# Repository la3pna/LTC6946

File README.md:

# LTC6946
LTC6946 PLL PCB + control library.

Made for using LTC6946 in the multisynth application with Si5351 as the clock generator (gives sub 1Hz resolution to 6GHz).

Does not seem to be finished, not sure if there is lacking some code? (dec 28, 2018)

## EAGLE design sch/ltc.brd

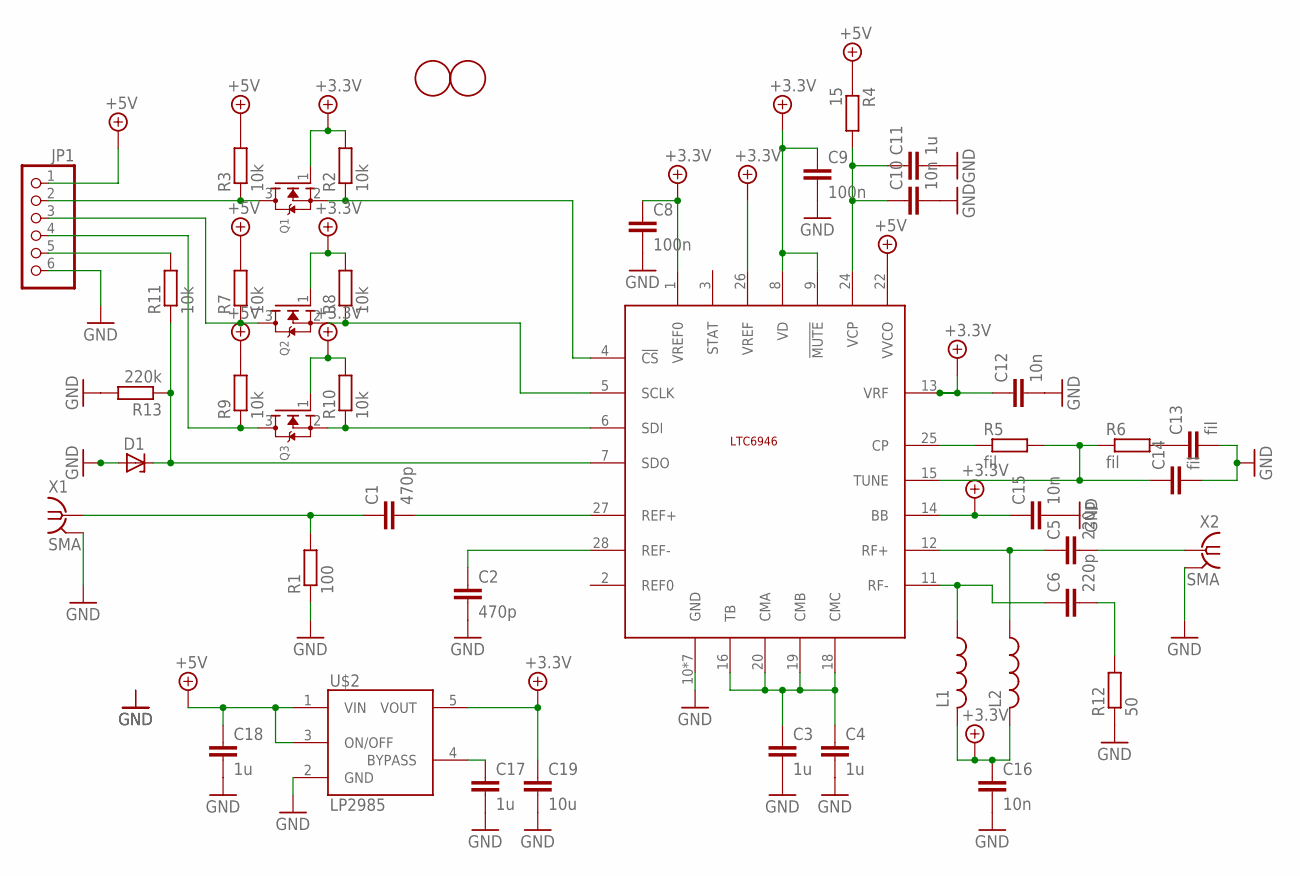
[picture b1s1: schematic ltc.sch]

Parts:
C1, C2: 470p; C0603
C3, C4, C11, C17, C18: 1u; C0603
C5, C6: 220p; C0603
C8, C9: 100n; C0603
C10, C12, C15, C16: 10n; C0603
C13, C14: fil; C0603
C19: 10u; C0603
D1: ZENER-DIODESOT23; SOT23
JP1: PINHD-1X6B; 1X06-BIG
L1, L2: L-USL2825P; L2825P
Q1, Q2, Q3: MOSFET-NREFLOW; SOT23
R1: 100; R0603
R2, R3, R7, R8, R9, R10, R11: 10k; R0603
R4: 15; R0603
R5, R6: fil; R0603
R12: 50; R0603
R13: 220k; R0603
U$1: LTC6946; QFN28-UFD
U$2: LP2985AIM5-3.3; SOT25
U$3, U$4: FIDUCIAL; FIDUCIAL_1MM
X1, X2: SMA; J502-ND-142-0711-821/826

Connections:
+4.1V: C8.1, C9.1, C12.1, C15.1, C16.1, C19.1, L1.2, L2.2, Q1.1 (G), Q2.1 (G), Q3.1 (G), R2.2, R8.2, R10.2, U$1.1 (VREF0), U$1.8 (VD), U$1.9 (!MUTE), U$1.13 (VRF), U$1.14 (BB), U$1.26 (VREF), U$2.5 (VOUT)
+5V: C18.1, JP1.1, R3.2, R4.1, R7.2, R9.2, U$1.22 (VVCO), U$2.1 (VIN), U$2.3 (ON/OFF)
BYPASS: C17.1, U$2.4 (BYPASS)
GND: C2.2, C3.2, C4.2, C8.2, C9.2, C10.2, C11.2, C12.2, C13.2, C14.2, C15.2, C16.2, C17.2, C18.2, C19.2, D1.1 (A), JP1.6, R1.1, R12.1, R13.2, U$1.10 (GND), U$1.17 (GND), U$1.21 (GND), U$1.23 (GND), U$1.29 (GND), U$1.29@1 (GND), U$1.29@2 (GND), U$2.2 (GND), X1.G@1 (2), X1.G@2 (2), X1.G@3 (2), X1.G@4 (2), X2.G@1 (2), X2.G@2 (2), X2.G@3 (2), X2.G@4 (2)
unnamed: C2.1, U$1.28 (REF-)
unnamed: C1.2, U$1.27 (REF+)
unnamed: C1.1, R1.2, X1.1
unnamed: C3.1, C4.1, U$1.16 (TB), U$1.18 (CMC), U$1.19 (CMB), U$1.20 (CMA)
unnamed: C6.2, R12.2
unnamed: Q1.2 (S), R2.1, U$1.4 (!CS)
unnamed: JP1.2, Q1.3 (D), R3.1
unnamed: C10.1, C11.1, R4.2, U$1.24 (VCP)
unnamed: Q2.2 (S), R8.1, U$1.5 (SCLK)
unnamed: JP1.3, Q2.3 (D), R7.1
unnamed: C13.1, R6.2
unnamed: C14.1, R5.2, R6.1, U$1.15 (TUNE)
unnamed: R5.1, U$1.25 (CP)
unnamed: C6.1, L1.1, U$1.11 (RF-)
unnamed: Q3.2 (S), R10.1, U$1.6 (SDI)
unnamed: C5.1, L2.1, U$1.12 (RF+)
unnamed: JP1.4, Q3.3 (D), R9.1
unnamed: D1.3 (C), R11.1, R13.1, U$1.7 (SDO)
unnamed: C5.2, X2.1
unnamed: JP1.5, R11.2

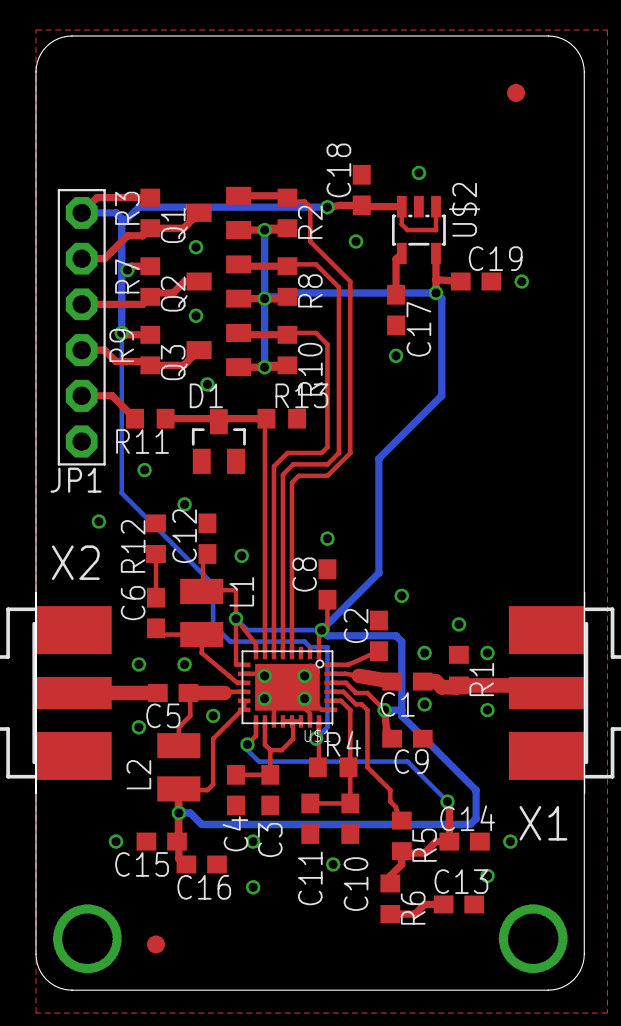
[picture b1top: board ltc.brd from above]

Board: 2 copper layers, 30.5 x 53.0 mm, 44 parts (0 on the bottom side), 24 nets.

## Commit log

2017-01-24 code
2017-01-24 setOdiv part
2017-02-22 schematic and brd
